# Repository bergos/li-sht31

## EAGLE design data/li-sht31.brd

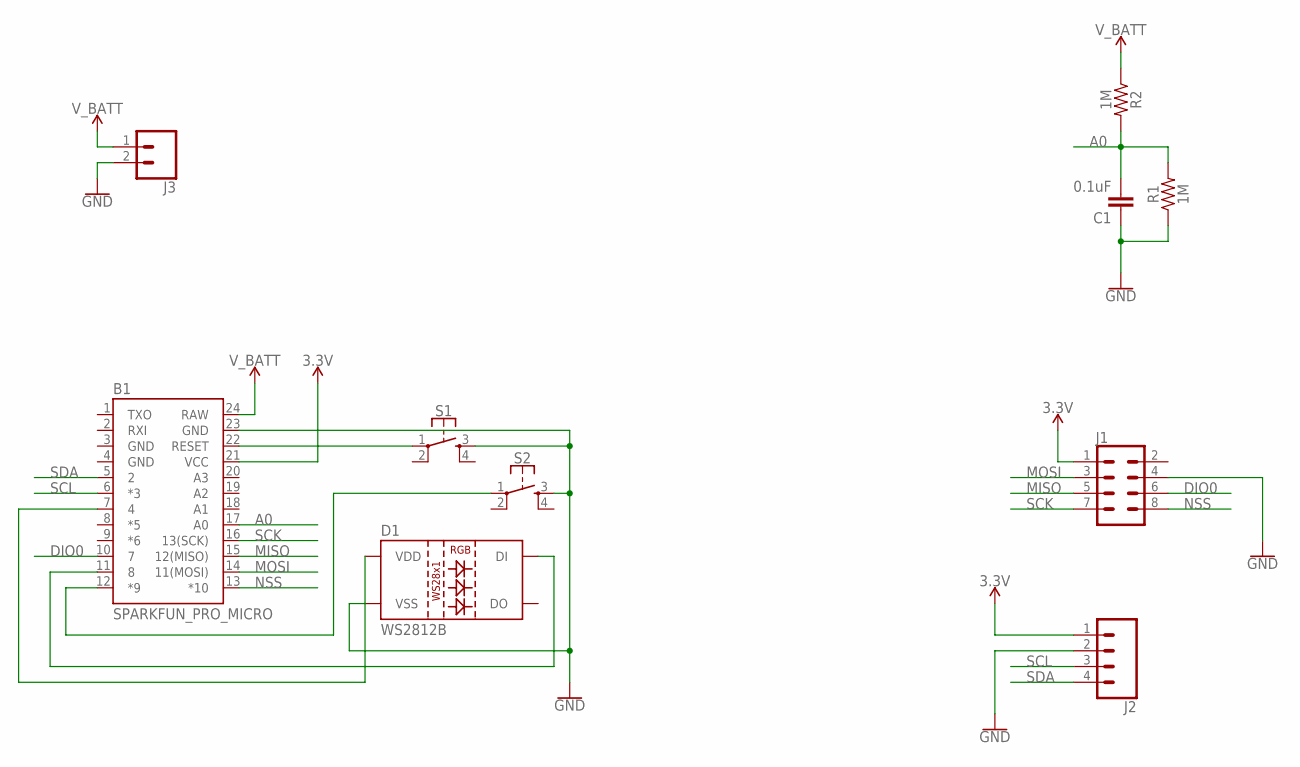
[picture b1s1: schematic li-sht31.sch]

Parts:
B1: SPARKFUN_PRO_MICRO
C1: 0.1uF; 0603
D1: WS2812B
J1: CONN_04X2; 2X4
J2: CONN_04; 1X04
J3: CONN_02; 1X02
R1, R2: 1M; 0603
S1, S2: MOMENTARY-SWITCH-SPST-2-SMD-5.2MM; TACTILE_SWITCH_SMD_5.2MM

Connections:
3.3V: B1.21 (VCC), J1.1, J2.1
A0: B1.17 (A0), C1.2, R1.2, R2.2
DIO0: B1.10 (7), J1.6
MISO: B1.15 (12(MISO)), J1.5
MOSI: B1.14 (11(MOSI)), J1.3
unnamed: B1.11 (8), D1.4 (DI)
unnamed: B1.3 (GND), B1.4 (GND), B1.23 (GND), C1.1, D1.3 (VSS), J1.4, J2.2, J3.2, R1.1, S1.3, S2.3
unnamed: B1.7 (4), D1.1 (VDD)
unnamed: B1.12 (*9), S2.1
unnamed: B1.22 (RESET), S1.1
NSS: B1.13 (*10), J1.8
SCK: B1.16 (13(SCK)), J1.7
SCL: B1.6 (*3), J2.3
SDA: B1.5 (2), J2.4
V_BATT: B1.24 (RAW), J3.1, R2.1

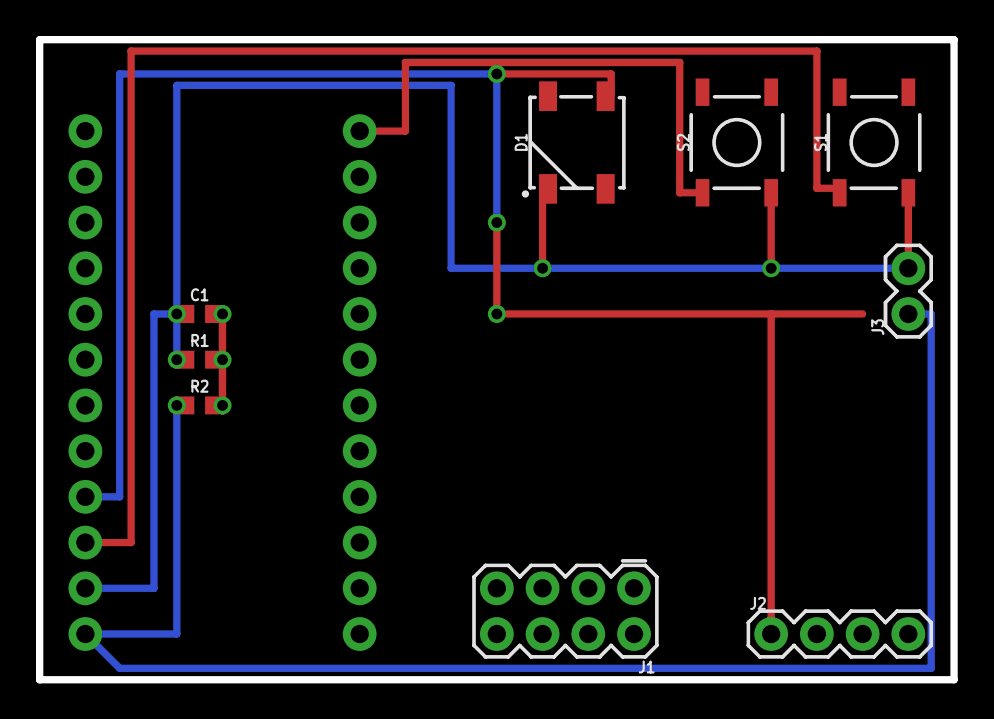
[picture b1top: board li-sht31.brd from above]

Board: 2 copper layers, 50.8 x 35.6 mm, 10 parts (0 on the bottom side), 15 nets.

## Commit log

2017-10-01 added hardware description as eagle schema and board

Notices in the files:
parts and their libraries:
SparkFun-Boards: Licensing: Creative Commons ShareAlike 4.0 International - https://creativecommons.org/licenses/by-sa/4.0
